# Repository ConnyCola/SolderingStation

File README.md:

# SolderingStation
Schemetics and Code for a DIY weller soldering station
Find more infos at https://debugginglab.wordpress.com/2014/10/30/soldering-station/

If ST7735_GREY is not found, add the following line to Adafruit_ST7735.h (e.g. line 124):

 #define ST7735_GREY    0x632C

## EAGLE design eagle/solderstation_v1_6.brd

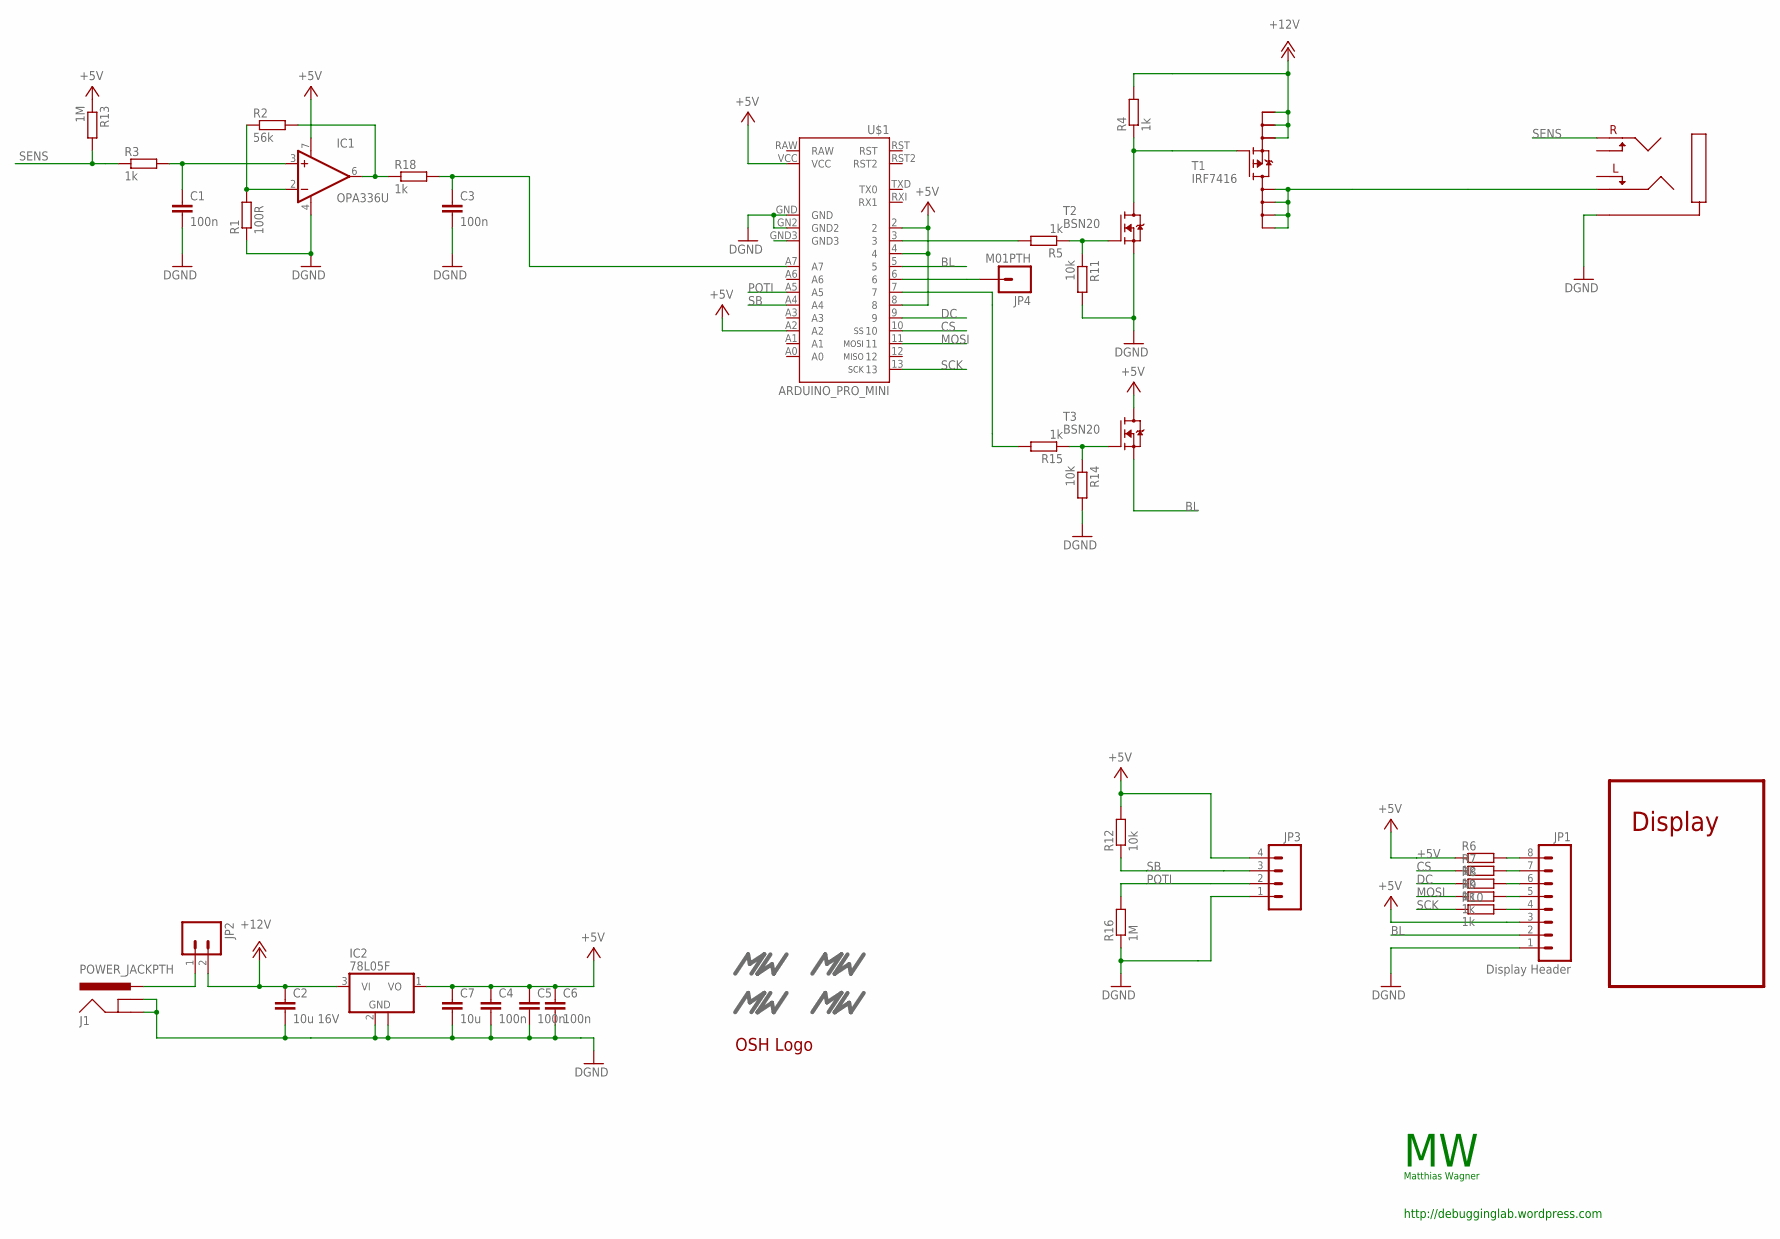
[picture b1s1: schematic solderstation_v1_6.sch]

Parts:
C1, C3, C4, C5, C6: 100n; C0603
C2: 10u 16V; C1206
C7: 10u; C1206
IC1: OPA336U; SO08
IC2: 78L05F; SOT89
J1: POWER_JACKPTH; POWER_JACK_PTH
JP1: Display Header; 1X08_LOCK
JP2: M02LOCK_LONGPADS; 1X02_LOCK_LONGPADS
JP3: M04LOCK; 1X04_LOCK
JP4: M01PTH; 1X01
R1: 100R; R0603
R2: 56k; R0603
R3, R4, R5, R6, R7, R8, R9, R10, R15, R18: 1k; R0603
R11, R12, R14: 10k; R0603
R13, R16: 1M; R0603
T1: IRF7416; SO8
T2, T3: BSN20; SOT23
U$1: ARDUINO_PRO_MINI
U$2: AUDIO_JACK_3,5MMCONRAD; AUDIO_JACK_3,5MM_CONRAD
U$3, U$5: MW_LOGO; MW_11X5MM
U$4, U$9: MW_LOGO_SOLDER; MW_11X5MM_SOLDER
U$8: OSH_LOGOS; OSH_LOGO_S

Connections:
+5V: C4.1, C5.1, C6.1, C7.1, IC1.7 (V+), IC2.1 (VO), JP1.3, JP3.4, R6.1, R12.2, R13.1, T3.3 (D), U$1.2, U$1.4, U$1.8, U$1.A2, U$1.VCC
+12V: C2.1, IC2.3 (VI), JP2.2, R4.2, T1.1 (S0), T1.2 (S1), T1.3 (S2)
BL: JP1.2, T3.2 (S), U$1.5
CS: R7.1, U$1.10
DC: R8.1, U$1.9
DGND: C1.2, C2.2, C3.2, C4.2, C5.2, C6.2, C7.2, IC1.4 (V-), IC2.2 (GND), IC2.2@1 (GND), J1.GND, J1.GNDBREAK, JP1.1, JP3.1, R1.1, R11.2, R14.2, R16.1, T2.2 (S), U$1.GN2 (GND2), U$1.GND, U$2.P_GND
HEATER: T1.5 (D0), T1.6 (D1), T1.7 (D2), T1.8 (D3), U$2.P_LEFT
MOSI: R9.1, U$1.11
unnamed: IC1.2 (-IN), R1.2, R2.1
unnamed: IC1.6 (OUT), R2.2, R18.1
unnamed: R5.1, R11.1, T2.1 (G)
unnamed: C1.1, IC1.3 (+IN), R3.2
unnamed: R4.1, T1.4 (G), T2.3 (D)
unnamed: JP1.4, R10.2
unnamed: R5.2, U$1.3
unnamed: JP1.5, R9.2
unnamed: JP1.6, R8.2
unnamed: JP1.7, R7.2
unnamed: JP1.8, R6.2
unnamed: J1.PWR, JP2.1
unnamed: R14.1, R15.1, T3.1 (G)
unnamed: R15.2, U$1.7
unnamed: JP4.1, U$1.6
unnamed: C3.1, R18.2, U$1.A7
POTI: JP3.2, R16.2, U$1.A5
SB: JP3.3, R12.1, U$1.A4
SCK: R10.1, U$1.13
SENS: R3.1, R13.2, U$2.P_RIGHT

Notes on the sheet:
Display
http://debugginglab.wordpress.com
Matthias Wagner

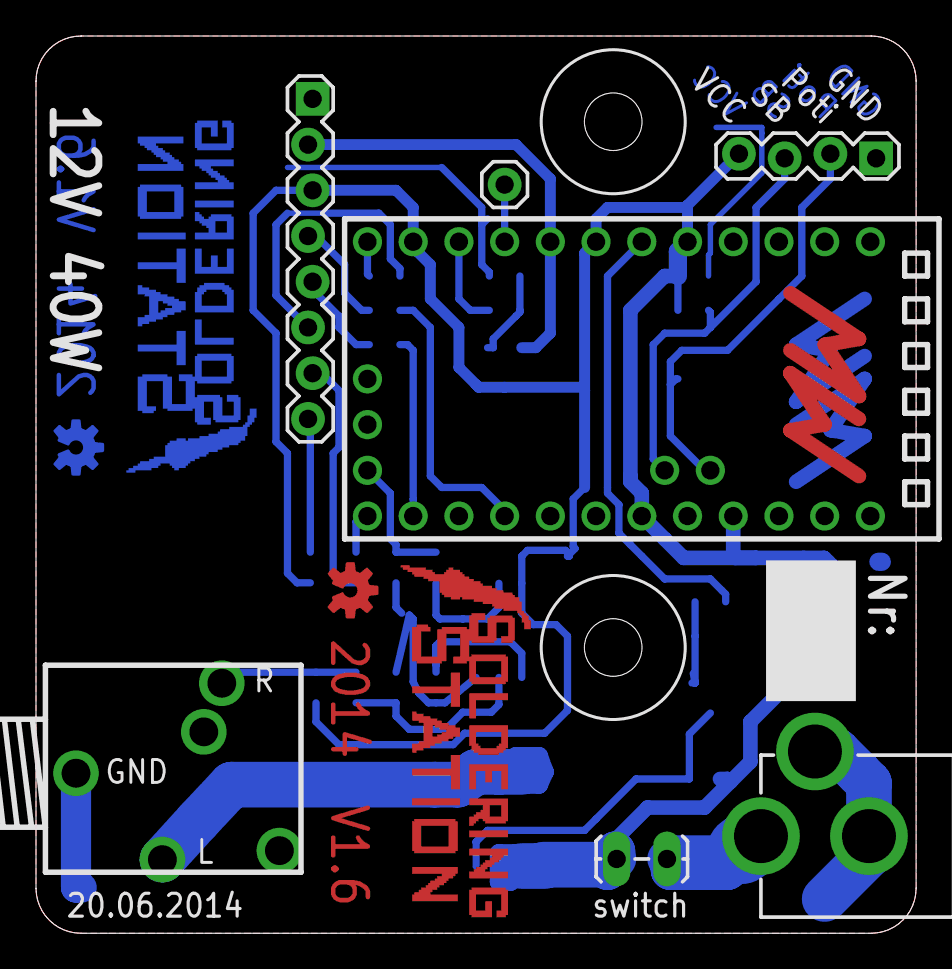
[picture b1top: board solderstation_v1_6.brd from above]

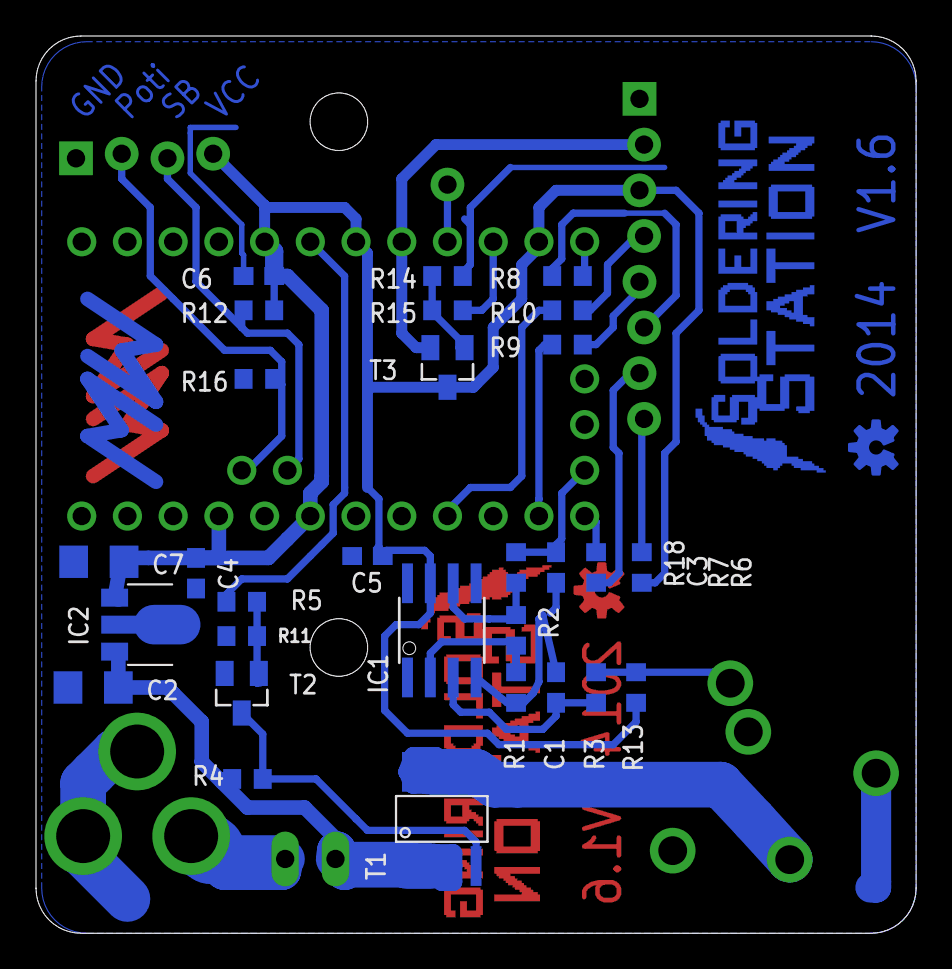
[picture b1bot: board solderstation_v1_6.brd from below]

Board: 2 copper layers, 48.9 x 49.8 mm, 44 parts (33 on the bottom side), 28 nets.

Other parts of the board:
U$6, U$7: SOLDER_STATION19,5MM_BOT; SOLDER_STATION_19,5MM_BOT
U$10: OSH_LOGOS; OSH_LOGO_S

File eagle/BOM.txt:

eagle/solderstation/solderstation_v1_6.sch am 02.07.15 01:52

Bestückungsvariante: 

count Value                  Device                 Component                                 
1                            M02LOCK_LONGPADS       JP2                                      
1                            M04LOCK                JP3                                      
2     1M                     R-EU_R0603             R13, R16                                 
10    1k                     R-EU_R0603             R3, R4, R5, R6, R7, R8, R9, R10, R15, R18
3     10k                    R-EU_R0603             R11, R12, R14                            
1     10u 6V                 C-EUC1206              C7                                       
1     10u 16V                C-EUC1206              C2                                       
1     56k                    R-EU_R0603             R2                                       
1     78L05F                 78L05F                 IC2                                      
1     100R                   R-EU_R0603             R1                                       
5     100n                   C-EUC0603              C1, C3, C4, C5, C6                       
1     ARDUINO_PRO_MINI       ARDUINO_PRO_MINI       U$1                                      
1     AUDIO_JACK_3,5MMCONRAD AUDIO_JACK_3,5MMCONRAD U$2                                      
2     BSN138                 BSN20                  T2, T3                                   
1     Display Header         M08LOCK                JP1                                      
1     IRF7416                IRF7416                T1                                       
1     M01PTH                 M01PTH                 JP4                                      
2     MW_LOGO                MW_LOGO                U$3, U$5                                 
2     MW_LOGO_SOLDER         MW_LOGO_SOLDER         U$4, U$9                                 
1     OPA336U                OPA336U                IC1                                      
1     OSH_LOGOS              OSH_LOGOS              U$8                                      
1     POWER_JACKPTH          POWER_JACKPTH          J1                                       



Bauteilliste				
				
count	Name				Store		No.	 			Price 
1		Arduino Pro Mini		Banggood	SKU066315	 	2,71 € 
1		TFT 160x128				Banggood	SKU103769	 	3,23 € 
					
1		3,5mm pcb Buchse		Conrad		734101	 		1,10 € 
1		3,5mm Buchse			Conrad		595223		 	1,09 € 
1		3,5mm Stecker			mouser		568-NYS231	 	0,82 € 
1		12V Jack				Conrad		735742	 		0,58 € 
1		opa336					mouser		595-OPA336UA	1,72 € 
1		irf7416					mouser		942-IRF7416PBF	1,07 € 
1		bss138					mouser		512-BSS138	 	0,18 € 
1		78L05					mouser		511-L78L05ABU	0,36 € 
1,15	LappKabel 1,15meter		Conrad		608304	 		2,44 € 
1		Main Switch				Banggood	SKU127477	 	0,58 € 
1		Poti 10k				Banggood	SKU047544	 	0,88 € 			
1		Netzteil 12V 8A			Banggood 					15,39 € 
4		Gummifüße 50stück		EBAY		 				0,30 € 			
1		PCB			 										1,40 € 
1		Weller RT 				mouser		 				32,56 € 
1		3D-Gehäuse	ALBERT		 							6,00 €

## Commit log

2014-10-30 first upload
2015-07-01 update with schematic
2015-07-01 added BOM
2015-07-01 BOM + StoreName
2015-07-20 new 3D files
    added the 3D files because of lots of questions for it
2015-07-20 added README.md
2015-10-20 Switched to ST7735 Display + beautification
    Switched to ST7735 display controller and added some coding style
2015-10-20 Added WS2812 support on AUX-pin
    A WS2812(B) RGB led attached to the aux pin of the board (and 5V + GND) is used to show the current state of the soldering station. Its color is the same as the text color on the lcd - fading from re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
2015-10-20 Modified top part to fit rotated banggood display
    Moved the display cutout to fit the meanwhile 180° rotated display.
2015-10-20 Extended inner space to fit arduino overhang
    The arduino overlaps the boards at the back, resulting in a gap when
    mounting the top cover. By reducing the thickness of the back, enough
    space is gained to fit the arduino inside. No changes to the top cover
    required, as the outer dimensions have not changed.
2015-11-28 changed image to be const
2015-11-28 changed images to be const
2015-11-28 Changed prog_uint8_t to uint8_t
    Due to recent changes in the Arduino IDE, prog_uin8_t is not defined anymore.
2015-11-28 Added missing color of ST7735 TFT lib
2015-11-28 Undo Changes
2016-06-07 Parts list cleanup
2016-07-12 Turn text wrap off
    Set TextWrap to false to get compatibility with different versions of the display
    tft.setTextWrap(false);

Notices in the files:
parts and their libraries:
SparkFun: Licensing: CC v3.0 Share-Alike You are welcome to use this library for commercial purposes.
